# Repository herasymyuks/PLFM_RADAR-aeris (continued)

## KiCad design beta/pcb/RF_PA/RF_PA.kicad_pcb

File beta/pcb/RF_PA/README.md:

# RF Power Amplifier (RF_PA) — BETA board

Project AERIS-10 · `beta/pcb/RF_PA/` · 2026-10-09 · **Status: BETA — KiCad-routed, DRC-checked, not reviewed by the original designer, not fabricated.**

Source of this copy: `engineering/PCB/RF_PA/kicad/RF_PA.kicad_pcb` (kicad-cli EAGLE import of `4_Schematics and Boards Layout/4_6_Schematics/PowerAmplifierBoard/RF_PA.brd`). The EAGLE originals and the engineering conversion were not modified.

## 1. Before / after

| Check | Before (engineering/PCB conversion) | After (BETA) |
|---|---|---|
| unconnected_items | 1 | 0 |
| clearance | 16 | 1 |
| shorting_items | 7 | 0 |
| silk_edge_clearance | 1 | 1 |
| silk_over_copper | 8 | 8 |
| silk_overlap | 8 | 8 |
| zones_intersect | 8 | 0 |
| **DRC violations total** | 48 | 18 |

Reports: `exports/reports/DRC_report.txt|json` (after), `engineering/PCB/RF_PA/reports/DRC_report.txt` (before).

## 2. What was changed (all logged, nothing in the netlist)

| # | Change | Tool / log | Why |
|---|---|---|---|
| 1 | GND strap F.Cu 0.5 mm from via (16.20, −11.20) to the QPA2962 ground paddle centre (16.20, −13.40) | `tools/beta_fix_stubs.py --extra`, `fixes.json` | the only unconnected item: the paddle was connected to the GND via field only through a net-less footprint polygon, which KiCad does not count as copper of the net |
| 2 | QPA2962 (U$1) footprint copper polygon (paddle, F.Cu) re-created as a board-level copper polygon with net **GND** and removed from the footprint — identical geometry | `tools/beta_polygon_nets.py --to-board`, `POLYGON_NET_DISPOSITION.md` | it touched 21 GND items and nothing else (unambiguous); as a net-less footprint graphic it produced 7 shorting + 19 hole-clearance + 15 clearance false errors |
| 3 | 6 overlapping GND zones on F.Cu given distinct priorities (same net, same outlines) | `tools/beta_zone_priorities.py`, `zone_priorities.json` | `zones_intersect` ×8 — equal-priority same-net overlap is only a KiCad ambiguity |
| 4 | Zones refilled, DRC re-run, package exported | `tools/beta_drc.sh`, `tools/beta_export_package.sh`, `exports/EXPORT_LOG.md` | |

RF tracks (`N$2`, `N$8` at 0.204 mm, bias lines) were **not** touched.

## 3. What remains (18 DRC items)

| Type | Count | Disposition |
|---|---|---|
| clearance | 1 | GND paddle polygon ↔ `VIN_M` track stub at (17.46, −15.63): 0.123 mm < 0.15 mm DRU. Exists in the source; RF/bias copper not modified in BETA → **designer to confirm or nudge the VIN_M stub** |
| silk_overlap | 8 | board texts `VIN+`/`VIN−` over the X3 connector outline; UNK22V0 footprint texts over its own outline — cosmetic |
| silk_over_copper | 8 | X2/X3 KK-connector outlines over their THT pads, J1/J2/U$1 silk over a mask-defined area — cosmetic, fab clips silk on pads |
| silk_edge_clearance | 1 | UNK22V0 reference field 0.1 mm from the board edge — cosmetic |

Unconnected: **0**. Unrouted list: none (`UNROUTED.md` not needed).

## 4. Files

`RF_PA.kicad_pcb` / `.kicad_pro` (BETA board), `BOM_RF_PA_beta.csv` (MPN proposals: 5 lines HIGH / 6 MEDIUM / 0 LOW / 0 EMPTY), `FAB_NOTES.md` (stack-up and impedance proposal), `POLYGON_NET_DISPOSITION.md`, `fixes.json`, `zone_priorities.json`, `exports/` (full package, see `FAB_NOTES.md` §5).

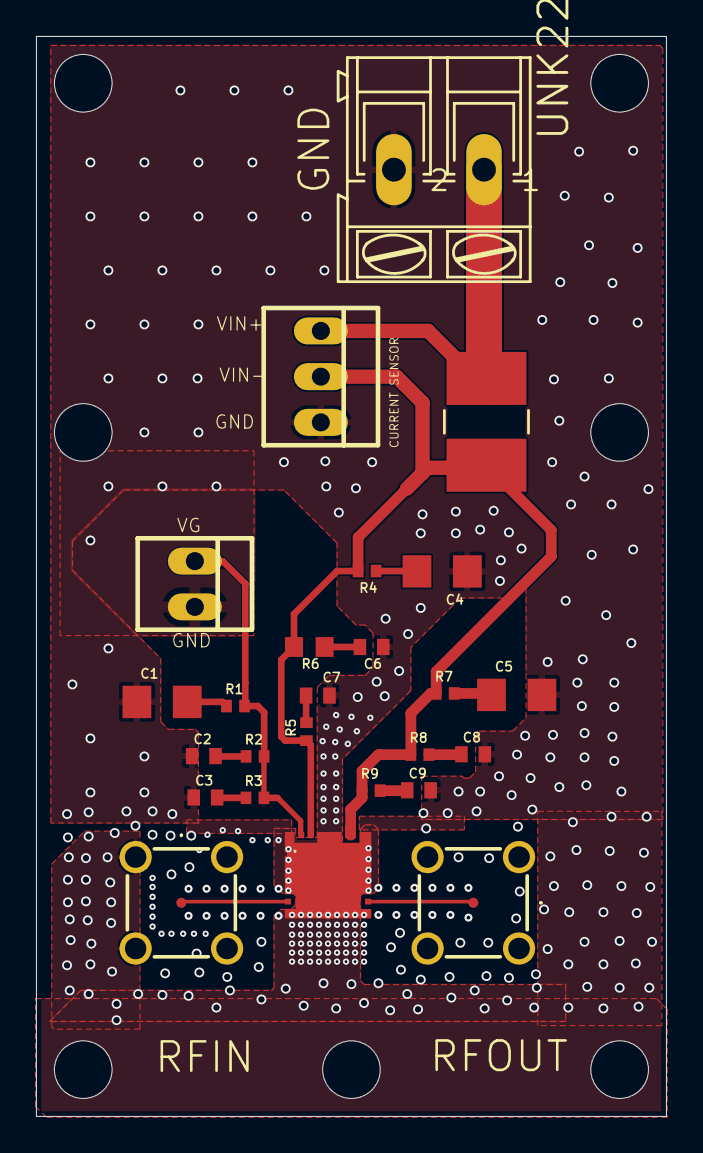
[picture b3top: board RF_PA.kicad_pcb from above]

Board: 4 copper layers, 35.0 x 60.0 mm, 32 parts (0 on the bottom side), 15 nets.

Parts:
C1, C4, C5: 10µF; C1206
C2, C3, C6, C7, C8, C9: 0.1µF; C0402
J1, J2: 142-0731-211; 1420731211
R1, R4: 10R; R0402
R2, R3, R5, R7, R8, R9: 0R; R0402
R6: 0R; R0603
R10: 5mR; WSL2816_VIS
U$1: QPA2962_B
UNK22V0: AK300_2
UNK_HOLE_0: dummyfp0
UNK_HOLE_1: dummyfp1
UNK_HOLE_2: dummyfp2
UNK_HOLE_3: dummyfp3
UNK_HOLE_4: dummyfp4
UNK_HOLE_5: dummyfp5
UNK_HOLE_6: dummyfp6
X2: 22-23-2021
X3: 22-23-2031

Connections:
GND: C1.1, C2.1, C3.1, C4.1, C5.2, C6.1, C7.1, C8.2, C9.2, J1.2, J1.3, J1.4, J1.5, J2.2, J2.3, J2.4, J2.5, U$1.GND, UNK22V0.2, X2.2, X3.3
unnamed: C3.2, R3.1
unnamed: J1.1, U$1.RFIN
unnamed: C1.2, R1.1
unnamed: C2.2, R2.1
unnamed: C4.2, R4.1
unnamed: C6.2, R6.1
unnamed: C7.2, R5.1
unnamed: J2.1, U$1.RFOUT
unnamed: C5.1, R7.2
unnamed: C8.1, R8.2
unnamed: C9.1, R9.2
VD: R10.2, UNK22V0.1, X3.1
VG: R1.2, R2.2, R3.2, U$1.VG, X2.1
VIN_M: R4.2, R5.2, R6.2, R7.1, R8.1, R9.1, R10.1, U$1.VD1, U$1.VD2, X3.2

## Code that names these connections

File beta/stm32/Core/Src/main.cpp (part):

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};

// Convenience HAL wrappers for AD9523 control pins (GPIOF as you said)
static inline void AD9523_PD(bool v)        { HAL_GPIO_WritePin(GPIOF, AD9523_PD_Pin, v ? GPIO_PIN_SET : GPIO_PIN_RESET); }
static inline void AD9523_REF_SEL(bool v)   { HAL_GPIO_WritePin(GPIOF, AD9523_REF_SEL_Pin, v ? GPIO_PIN_SET : GPIO_PIN_RESET); }
static inline void AD9523_SYNC_PULSE(void)  { HAL_GPIO_WritePin(GPIOF, AD9523_SYNC_Pin, GPIO_PIN_SET); HAL_Delay(1); HAL_GPIO_WritePin(GPIOF, AD9523_SYNC_Pin, GPIO_PIN_RESET); }
static inline void AD9523_RESET_ASSERT()    { HAL_GPIO_WritePin(GPIOF, AD9523_RESET_Pin, GPIO_PIN_RESET); } // check polarity
static inline void AD9523_RESET_RELEASE()   { HAL_GPIO_WritePin(GPIOF, AD9523_RESET_Pin, GPIO_PIN_SET); }
static inline void AD9523_CS(bool v)        { HAL_GPIO_WritePin(GPIOF, AD9523_CS_Pin, v ? GPIO_PIN_SET : GPIO_PIN_RESET); }
static inline void AD9523_EEPROM_SEL(bool v){ HAL_GPIO_WritePin(GPIOF, AD9523_EEPROM_SEL_Pin, v ? GPIO_PIN_SET : GPIO_PIN_RESET); }

/* USER CODE END PV */

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    // 1. Check AD9523 Clock Generator
    static uint32_t last_clock_check = 0;
    if (HAL_GetTick() - last_clock_check > 5000) {
        if (HAL_GPIO_ReadPin(AD9523_STATUS0_GPIO_Port, AD9523_STATUS0_Pin) == GPIO_PIN_RESET ||
            HAL_GPIO_ReadPin(AD9523_STATUS1_GPIO_Port, AD9523_STATUS1_Pin) == GPIO_PIN_RESET) {
            current_error = ERROR_AD9523_CLOCK;
        }
        last_clock_check = HAL_GetTick();
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  DWT_Init();
  //Wait for OCXO 3mn
  HAL_Delay(180000);
  HAL_GPIO_WritePin(AD9523_RESET_GPIO_Port,AD9523_RESET_Pin,GPIO_PIN_RESET);

  //Power sequencing AD9523
  HAL_GPIO_WritePin(EN_P_1V8_CLOCK_GPIO_Port,EN_P_1V8_CLOCK_Pin,GPIO_PIN_SET);
  HAL_Delay(100);
  HAL_GPIO_WritePin(EN_P_3V3_CLOCK_GPIO_Port,EN_P_3V3_CLOCK_Pin,GPIO_PIN_SET);
  HAL_Delay(100);
  HAL_GPIO_WritePin(AD9523_RESET_GPIO_Port,AD9523_RESET_Pin,GPIO_PIN_SET);
  HAL_Delay(100);

  //Set planned Clocks on AD9523
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                   rx_locked ? "LOCKED" : "UNLOCKED");
        }
  // check if there is a lock
  if(HAL_GPIO_ReadPin (ADF4382_TX_LKDET_GPIO_Port, ADF4382_TX_LKDET_Pin))
  {
      // Set The LED_1 ON!
      HAL_GPIO_WritePin(LED_1_GPIO_Port, LED_1_Pin, GPIO_PIN_SET);
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      HAL_GPIO_WritePin(LED_1_GPIO_Port, LED_1_Pin, GPIO_PIN_RESET);
  }

  if(HAL_GPIO_ReadPin (ADF4382_RX_LKDET_GPIO_Port, ADF4382_RX_LKDET_Pin))
  {
      // Set The LED_2 ON!
      HAL_GPIO_WritePin(LED_2_GPIO_Port, LED_2_Pin, GPIO_PIN_SET);
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  __HAL_RCC_GPIOD_CLK_ENABLE();

  /*Configure GPIO pin Output Level */
  HAL_GPIO_WritePin(GPIOF, AD9523_PD_Pin|AD9523_REF_SEL_Pin|AD9523_SYNC_Pin|AD9523_RESET_Pin
                          |AD9523_CS_Pin|AD9523_EEPROM_SEL_Pin|LED_1_Pin|LED_2_Pin
                          |LED_3_Pin|LED_4_Pin, GPIO_PIN_RESET);

  /*Configure GPIO pin Output Level */
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
  /*Configure GPIO pin Output Level */
  HAL_GPIO_WritePin(GPIOG, EN_P_5V0_PA1_Pin|EN_P_5V0_PA2_Pin|EN_P_5V0_PA3_Pin|EN_P_5V5_PA_Pin
                          |EN_P_1V8_CLOCK_Pin|EN_P_3V3_CLOCK_Pin|ADF4382_RX_DELADJ_Pin|ADF4382_RX_DELSTR_Pin
                          |ADF4382_RX_CE_Pin|ADF4382_RX_CS_Pin|ADF4382_TX_DELSTR_Pin|ADF4382_TX_DELADJ_Pin
                          |ADF4382_TX_CS_Pin|ADF4382_TX_CE_Pin, GPIO_PIN_RESET);

  /*Configure GPIO pin Output Level */
  HAL_GPIO_WritePin(GPIOE, EN_P_1V0_FPGA_Pin|EN_P_1V8_FPGA_Pin|EN_P_3V3_FPGA_Pin|EN_P_5V0_ADAR_Pin
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  /*Configure GPIO pin Output Level */
  HAL_GPIO_WritePin(GPIOB, DAC_1_VG_CLR_Pin|DAC_1_VG_LDAC_Pin|DAC_2_VG_CLR_Pin|DAC_2_VG_LDAC_Pin, GPIO_PIN_RESET);

  /*Configure GPIO pins : AD9523_PD_Pin AD9523_REF_SEL_Pin AD9523_SYNC_Pin AD9523_RESET_Pin
                           AD9523_CS_Pin AD9523_EEPROM_SEL_Pin LED_1_Pin LED_2_Pin
                           LED_3_Pin LED_4_Pin */
  GPIO_InitStruct.Pin = AD9523_PD_Pin|AD9523_REF_SEL_Pin|AD9523_SYNC_Pin|AD9523_RESET_Pin
                          |AD9523_CS_Pin|AD9523_EEPROM_SEL_Pin|LED_1_Pin|LED_2_Pin
                          |LED_3_Pin|LED_4_Pin;
  GPIO_InitStruct.Mode = GPIO_MODE_OUTPUT_PP;
  GPIO_InitStruct.Pull = GPIO_NOPULL;
  GPIO_InitStruct.Speed = GPIO_SPEED_FREQ_LOW;
  HAL_GPIO_Init(GPIOF, &GPIO_InitStruct);

  /*Configure GPIO pins : AD9523_STATUS0_Pin AD9523_STATUS1_Pin */
  GPIO_InitStruct.Pin = AD9523_STATUS0_Pin|AD9523_STATUS1_Pin;
  GPIO_InitStruct.Mode = GPIO_MODE_INPUT;
  GPIO_InitStruct.Pull = GPIO_NOPULL;
  HAL_GPIO_Init(GPIOF, &GPIO_InitStruct);
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  HAL_GPIO_Init(GPIOA, &GPIO_InitStruct);

  /*Configure GPIO pins : EN_P_5V0_PA1_Pin EN_P_5V0_PA2_Pin EN_P_5V0_PA3_Pin EN_P_5V5_PA_Pin
                           EN_P_1V8_CLOCK_Pin EN_P_3V3_CLOCK_Pin ADF4382_RX_DELADJ_Pin ADF4382_RX_DELSTR_Pin
                           ADF4382_RX_CE_Pin ADF4382_RX_CS_Pin ADF4382_TX_DELSTR_Pin ADF4382_TX_DELADJ_Pin
                           ADF4382_TX_CS_Pin ADF4382_TX_CE_Pin */
  GPIO_InitStruct.Pin = EN_P_5V0_PA1_Pin|EN_P_5V0_PA2_Pin|EN_P_5V0_PA3_Pin|EN_P_5V5_PA_Pin
                          |EN_P_1V8_CLOCK_Pin|EN_P_3V3_CLOCK_Pin|ADF4382_RX_DELADJ_Pin|ADF4382_RX_DELSTR_Pin
                          |ADF4382_RX_CE_Pin|ADF4382_RX_CS_Pin|ADF4382_TX_DELSTR_Pin|ADF4382_TX_DELADJ_Pin
                          |ADF4382_TX_CS_Pin|ADF4382_TX_CE_Pin;
  GPIO_InitStruct.Mode = GPIO_MODE_OUTPUT_PP;
  GPIO_InitStruct.Pull = GPIO_NOPULL;
  GPIO_InitStruct.Speed = GPIO_SPEED_FREQ_LOW;
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  GPIO_InitStruct.Pull = GPIO_NOPULL;
  HAL_GPIO_Init(GPIOD, &GPIO_InitStruct);

  /*Configure GPIO pins : ADF4382_RX_LKDET_Pin ADF4382_TX_LKDET_Pin */
  GPIO_InitStruct.Pin = ADF4382_RX_LKDET_Pin|ADF4382_TX_LKDET_Pin;
  GPIO_InitStruct.Mode = GPIO_MODE_INPUT;
  GPIO_InitStruct.Pull = GPIO_NOPULL;
  HAL_GPIO_Init(GPIOG, &GPIO_InitStruct);
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  /* USER CODE BEGIN MX_GPIO_Init_2 */
  /* BETA (D-05): SPI chip selects are active-low; park them HIGH (deasserted).
   * The generated code above drives them LOW, i.e. every slave permanently selected. */
  HAL_GPIO_WritePin(AD9523_CS_GPIO_Port, AD9523_CS_Pin, GPIO_PIN_SET);
  HAL_GPIO_WritePin(ADF4382_TX_CS_GPIO_Port, ADF4382_TX_CS_Pin, GPIO_PIN_SET);
  HAL_GPIO_WritePin(ADF4382_RX_CS_GPIO_Port, ADF4382_RX_CS_Pin, GPIO_PIN_SET);
  HAL_GPIO_WritePin(GPIOA, ADAR_1_CS_3V3_Pin|ADAR_2_CS_3V3_Pin|ADAR_3_CS_3V3_Pin|ADAR_4_CS_3V3_Pin, GPIO_PIN_SET);
  /* USER CODE END MX_GPIO_Init_2 */
}
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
